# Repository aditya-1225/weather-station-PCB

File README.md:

# PCB - weather station transceiver
This PCB uses an ATmega328P microcontroller to receive data from a BMP280 sensor module and to send it over to the nRF24L01+PA+LNA through SPI on the PCB or to a computer through a serial connection for logging/processing the air temperature and pressure data.

If the data is sent to the nRF24L01+PA+LNA module, another PCB acts as the receiver and transmits the received data to a computer through the serial port.

## ATmega328P - Overview
The ATmega328P runs at 16 MHz, controlled by an external crystal oscillator (Y1).

Its operating voltage is 5V.

## Circuit Design Notes
1. 300 ohm resistors are placed in series on the SPI lines between the nRF24L01+PA+LNA module and the MCU. This is done to ensure that the peripheral SPI device(nRF24L01+PA+LNA in this case) does not interfere with programming the MCU as it is programmed through the J3 connector using SPI-based In-system programming.

2. Two 4.7kΩ I2C pull-up resistors are placed on the SDA and SCL lines.

3. Stitching vias are placed on the board to help mitigate interference while the nRF24L01+PA+LNA module is operational.

4. A diode is placed between the power input of the J3 connector and PCB's power plane for reverse voltage protection.

5. An AMS1117 IC is used to convert the 5V input to 3.3V for the BMP280 and nRF24L01+PA+LNA.

6. A 100µF and a 0.1µF decoupling capacitor are placed on the 3.3V and 5V power rail. The 100µF handles large voltage transients while the 0.1µF filters high-frequency noise.

# Powering and programming the board
1. To power the board, a USB-C connector is placed at the top of the board. 
**NOTE:** This connector cannot be used for programming. It can only power the board

2. To program the microcontroller, the J3 connector is used. It is programmed using SPI-based In-system programming.

## Pinouts

1. J3

| Pin | Function |
|-----|----------|
| 1   | RX       |
| 2   | MISO     |
| 3   | TX       |
| 4   | MOSI     |
| 5   | SCK      |
| 6   | GND      |
| 7   | RESET    |
| 8   | +5V      |

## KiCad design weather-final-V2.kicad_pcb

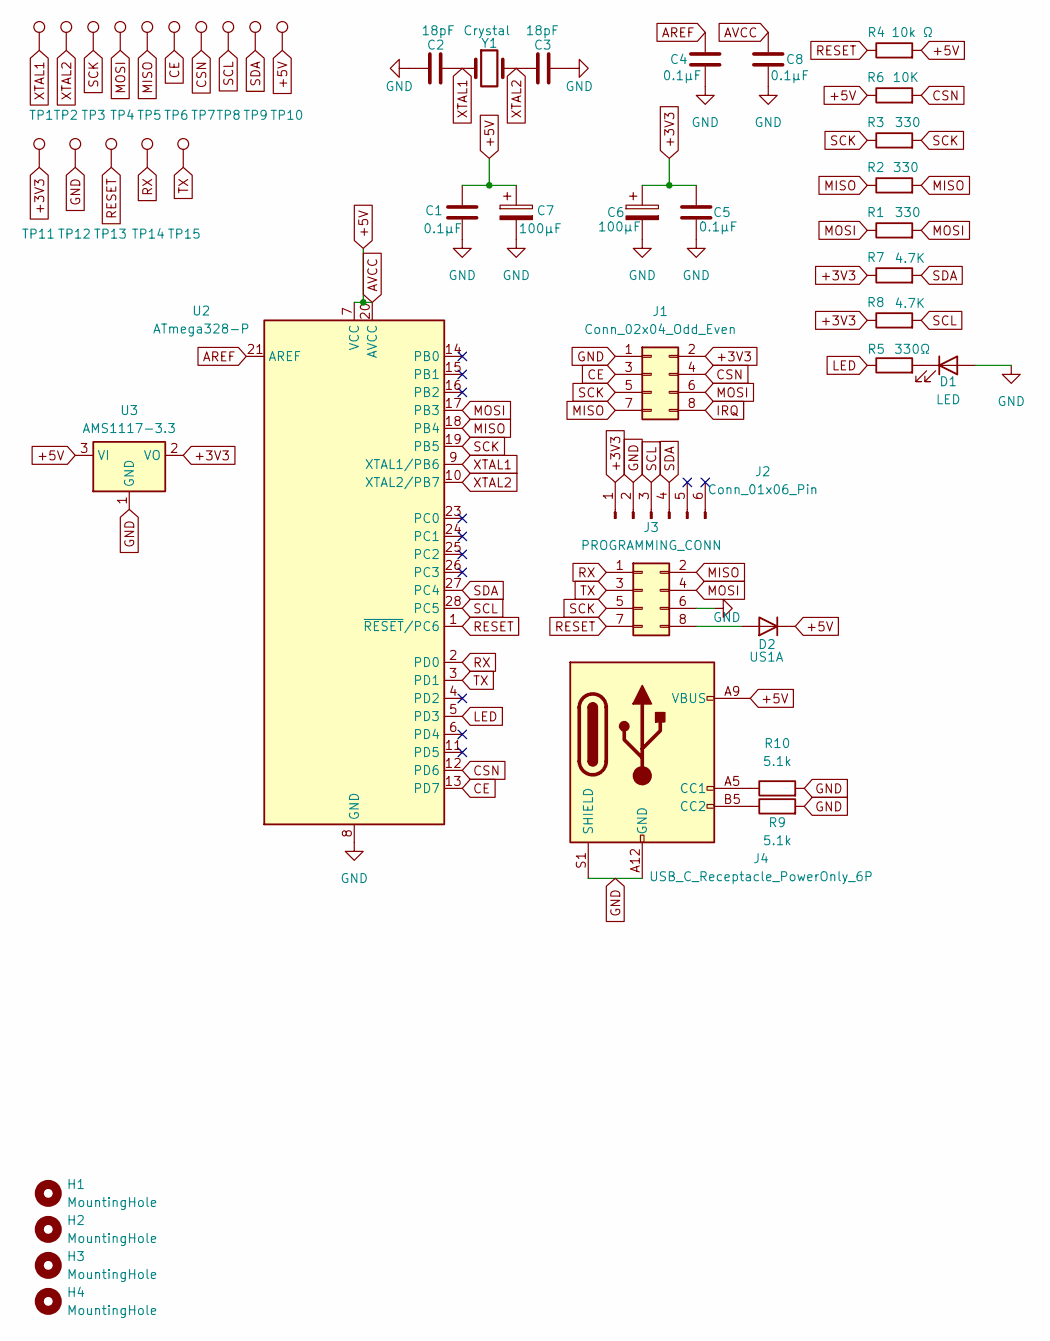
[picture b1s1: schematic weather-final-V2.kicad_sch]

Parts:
C1, C4, C5, C8: 0.1μF; C_1206_3216Metric_Pad1.33x1.80mm_HandSolder
C2, C3: 18pF; C_1206_3216Metric_Pad1.33x1.80mm_HandSolder
C6, C7: 100μF; CP_Radial_D5.0mm_P2.00mm
D1: LED; LED_1206_3216Metric_Pad1.42x1.75mm_HandSolder
D2: US1A; D_SMA
H1, H2, H3, H4: MountingHole; MountingHole_2mm
J1: Conn_02x04_Odd_Even; PinHeader_2x04_P2.54mm_Vertical
J2: Conn_01x06_Pin; PinHeader_1x06_P2.54mm_Vertical
J3: PROGRAMMING_CONN; PinHeader_2x04_P2.54mm_Vertical
J4: USB_C_Receptacle_PowerOnly_6P; USB_C_Receptacle_HRO_TYPE-C-31-M-17
R1, R2, R3: 330; R_1206_3216Metric_Pad1.30x1.75mm_HandSolder
R4: 10k Ω; R_1206_3216Metric_Pad1.30x1.75mm_HandSolder
R5: 330Ω; R_1206_3216Metric_Pad1.30x1.75mm_HandSolder
R6: 10K; R_1206_3216Metric_Pad1.30x1.75mm_HandSolder
R7, R8: 4.7K; R_1206_3216Metric_Pad1.30x1.75mm_HandSolder
R9, R10: 5.1k; R_1206_3216Metric_Pad1.30x1.75mm_HandSolder
TP1, TP2, TP3, TP4, TP5, TP6, TP7, TP8, TP9, TP10, TP11, TP12, TP13, TP14, TP15: TestPoint; TestPoint_Pad_D1.0mm
U2: ATmega328-P; DIP-28_W7.62mm_Socket
U3: AMS1117-3.3; SOT-223-3_TabPin2
Y1: Crystal; Crystal_HC49-U_Vertical

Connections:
+3V3: C5.1, C6.1, J1.2, J2.1, R7.1, R8.1, TP11.1 (1_1), U3.2 (VO)
+5V: C1.1, C7.1, C8.2, D2.1 (K), J4.A9 (VBUS), J4.B9 (VBUS), R4.2, R6.1, TP10.1 (1_1), U2.7 (VCC), U2.20 (AVCC), U3.3 (VI)
AREF: C4.1, U2.21 (AREF)
CE: J1.3, TP6.1 (1_1), U2.13 (PD7)
CSN: J1.4, R6.2, TP7.1 (1_1), U2.12 (PD6)
GND: C1.2, C2.2, C3.2, C4.2, C5.2, C6.2, C7.2, C8.1, D1.2 (A), J1.1, J2.2, J3.6, J4.A12 (GND), J4.B12 (GND), J4.S1 (SHIELD), R9.2, R10.2, TP12.1 (1_1), U2.8 (GND), U2.22 (GND), U3.1 (GND)
IRQ: J1.8
LED: R5.1, U2.5 (PD3)
MISO: J1.7, J3.2, R2.1, R2.2, TP5.1 (1_1), U2.18 (PB4)
MOSI: J1.6, J3.4, R1.1, R1.2, TP4.1 (1_1), U2.17 (PB3)
unnamed: D1.1 (K), R5.2
unnamed: D2.2 (A), J3.8
unnamed: J4.A5 (CC1), R10.1
unnamed: J4.B5 (CC2), R9.1
RESET: J3.7, R4.1, TP13.1 (1_1), U2.1 (~RESET/PC6)
RX: J3.1, TP14.1 (1_1), U2.2 (PD0)
SCK: J1.5, J3.5, R3.1, R3.2, TP3.1 (1_1), U2.19 (PB5)
SCL: J2.3, R8.2, TP8.1 (1_1), U2.28 (PC5)
SDA: J2.4, R7.2, TP9.1 (1_1), U2.27 (PC4)
TX: J3.3, TP15.1 (1_1), U2.3 (PD1)
XTAL1: C2.1, TP1.1 (1_1), U2.9 (XTAL1/PB6), Y1.1
XTAL2: C3.1, TP2.1 (1_1), U2.10 (XTAL2/PB7), Y1.2

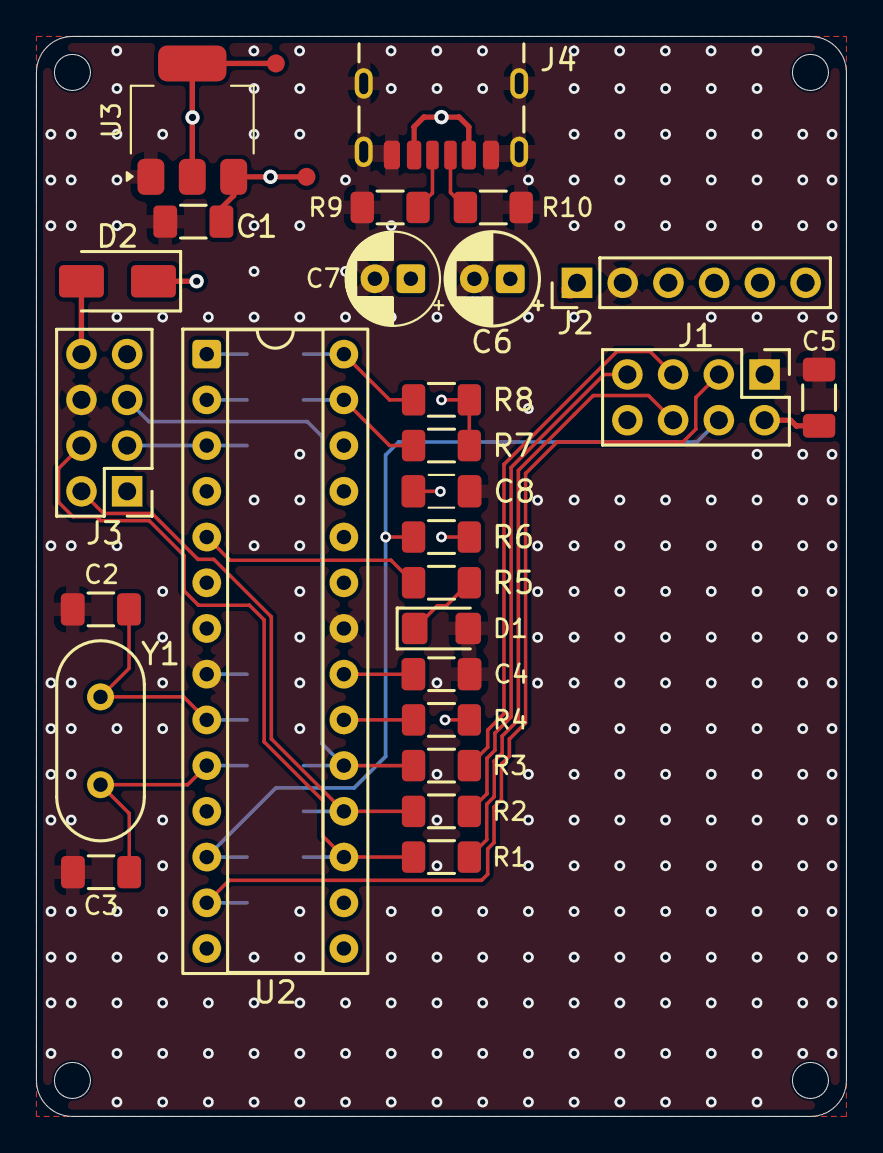
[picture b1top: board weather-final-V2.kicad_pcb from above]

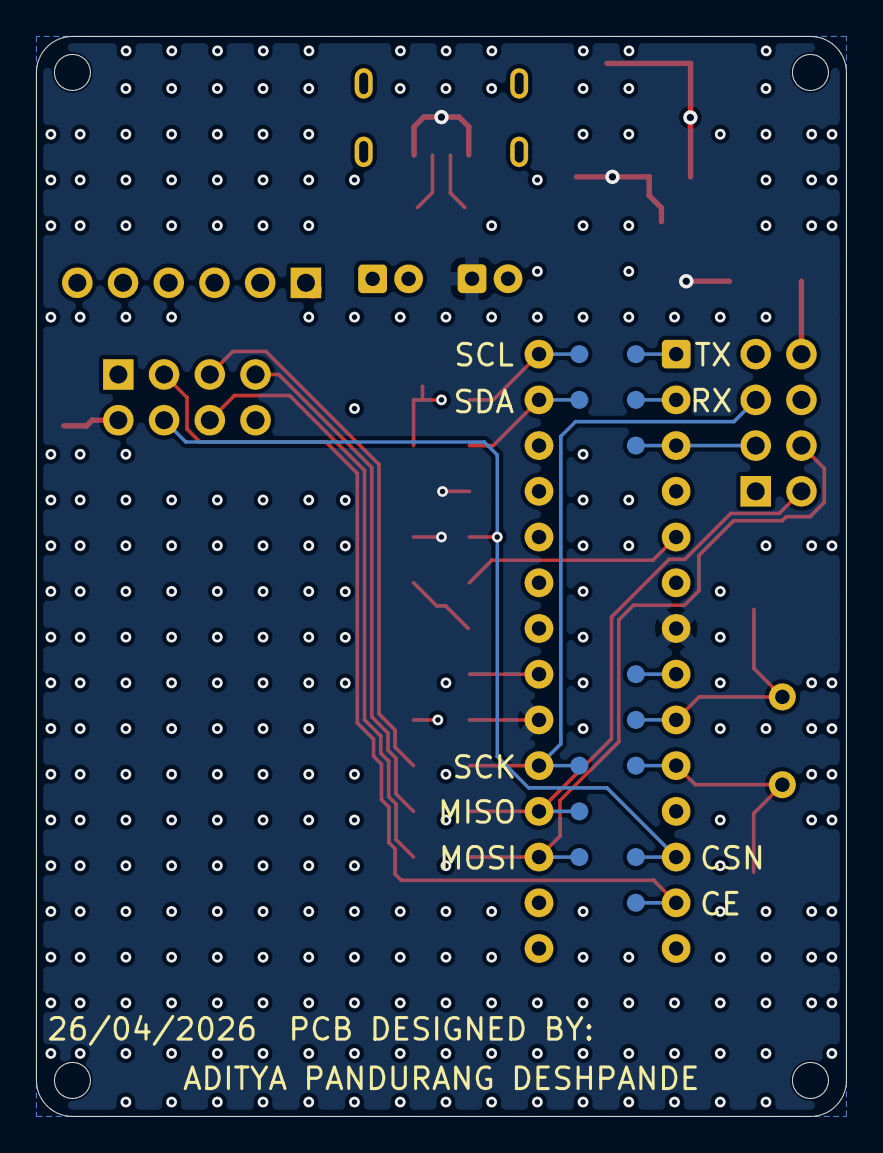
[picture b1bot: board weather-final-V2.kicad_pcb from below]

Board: 4 copper layers, 45.0 x 60.0 mm, 46 parts (13 on the bottom side), 21 nets.

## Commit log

2026-04-17 initial commit - weather PCB V2
2026-04-19 Add 2 more layers to PCB - 3V3 and GND. Route some signal traces in 3rd layer to get continuous GND plane on top and 5V plane in bottom. Remove unnecessary traces.
2026-04-20 Add i2c pullups Clean unnecessary trace widths Add diode for reverse voltage protection on J3 input
2026-04-21 Edit silkscreen width and positions
2026-04-22 Add stitching vias
2026-04-23 Add board-edge stitching vias
2026-04-24 Add i2c pullup resistors' values Fix a silkscreen overlap
2026-04-26 Add a 5V power rail decoupling capacitor Add LICENSE and README
2026-05-07 Add AVCC decoupling capacitor, Change symbol of 5V to 3V3 converter from AMS1117-5.0 to AMS1117-3.3, Clean up schematics
